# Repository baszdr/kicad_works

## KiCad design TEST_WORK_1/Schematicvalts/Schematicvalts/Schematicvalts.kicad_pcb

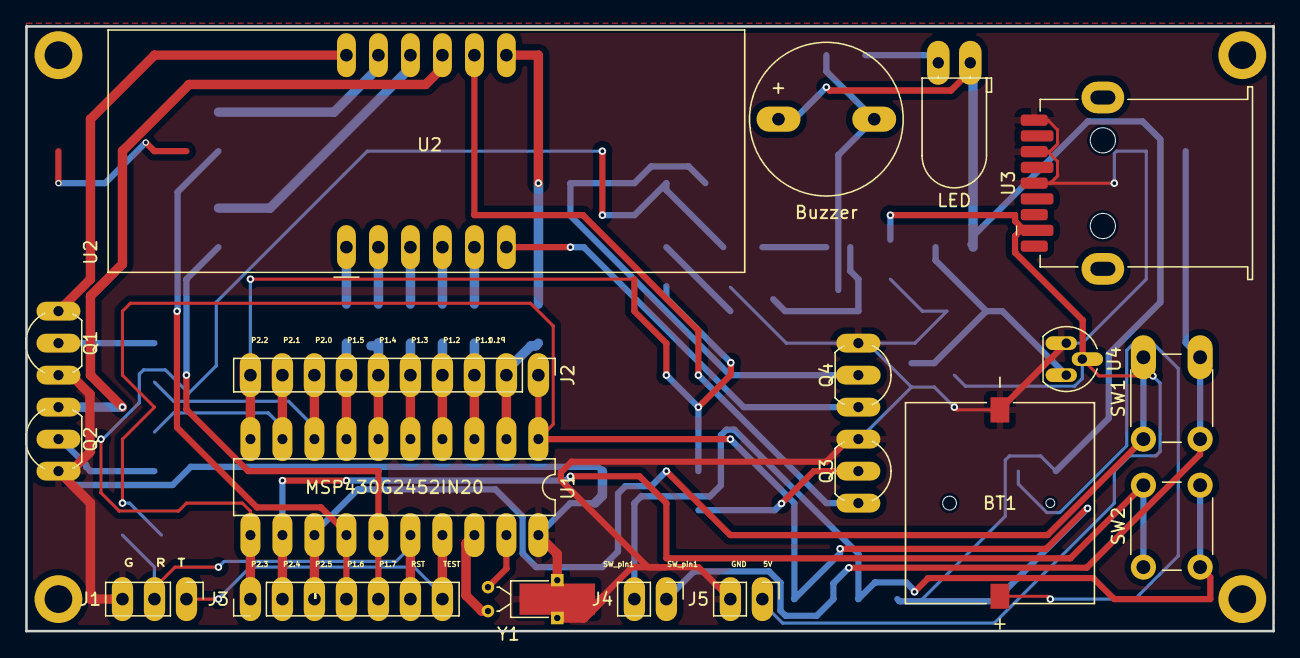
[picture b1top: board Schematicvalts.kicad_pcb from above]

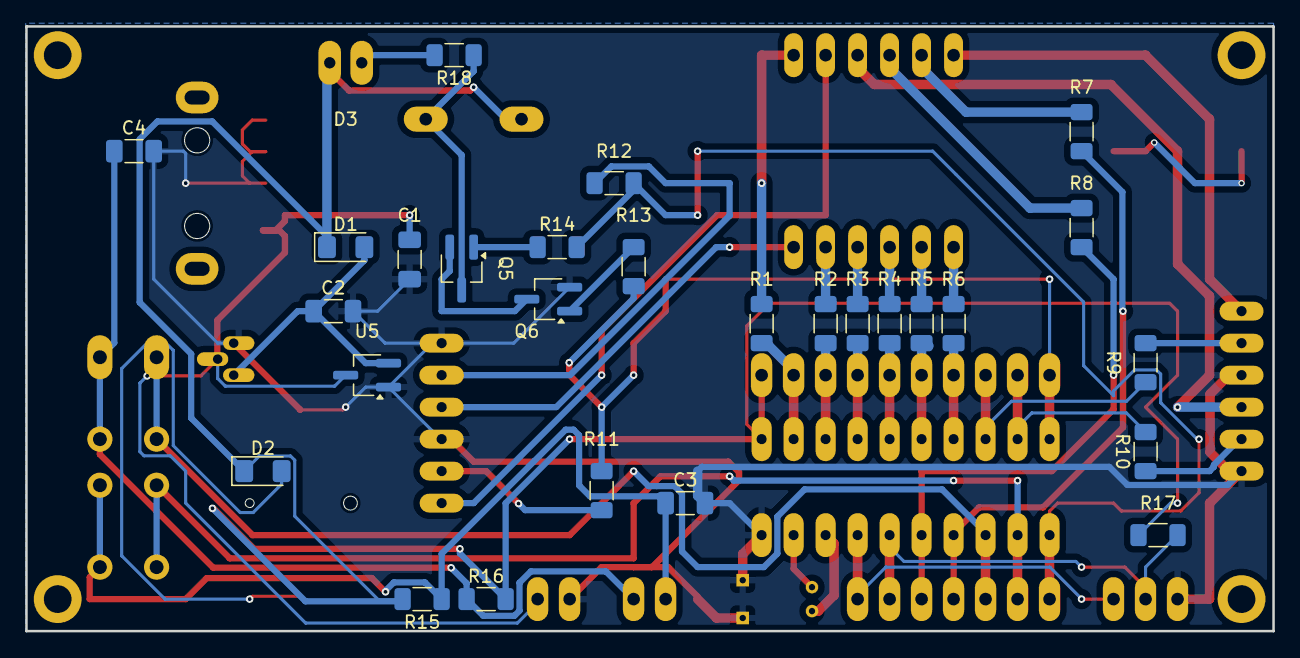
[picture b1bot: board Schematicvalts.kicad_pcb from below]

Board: 2 copper layers, 99.0 x 48.0 mm, 50 parts (27 on the bottom side), 46 nets.

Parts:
BT1: 1072; BAT_1072
BZ1: Buzzer; Buzzer_12x9.5RM7.6
C1, C2: 1uF; C_1206_3216Metric_Pad1.33x1.80mm_HandSolder
C3, C4: 470nF; C_1206_3216Metric_Pad1.33x1.80mm_HandSolder
D1, D2: D_Small; D_1206_3216Metric_Pad1.42x1.75mm_HandSolder
D3: LED; LED_D5.0mm_Horizontal_O1.27mm_Z3.0mm_Clear
H1, H2, H3, H4: MountingHole_Pad; MountingHole_2.2mm_M2_DIN965_Pad
J1: Conn_01x03_Socket; PinHeader_1x03_P2.54mm_Vertical
J2: Conn_01x10_Socket; PinHeader_1x10_P2.54mm_Vertical
J3: Conn_01x07_Socket; PinHeader_1x07_P2.54mm_Vertical
J4, J5: Conn_01x02_Socket; PinHeader_1x02_P2.54mm_Vertical
Q1, Q2, Q3, Q4: 2N3904; TO-92_Inline_Wide
Q5, Q6: MMBT3904; SOT-23W_Handsoldering
R1, R2, R3, R4, R5, R6, R7, R8: 300; R_1206_3216Metric_Pad1.30x1.75mm_HandSolder
R9, R10, R11, R12, R13, R14: 2.2k; R_1206_3216Metric_Pad1.30x1.75mm_HandSolder
R15, R16: 33k; R_1206_3216Metric_Pad1.30x1.75mm_HandSolder
R17: 51k; R_1206_3216Metric_Pad1.30x1.75mm_HandSolder
R18: 1K; R_1206_3216Metric_Pad1.30x1.75mm_HandSolder
SW1, SW2: SW_Push; SW_PUSH_6mm_H4.3mm
U1: MSP430G2452IN20; DIP-20_W7.62mm_LongPads
U2: CA56-12EWA
U3: 548190519; USB3_A_Receptacle_Wuerth_692122030100
U4: MCP1700x-120xxTO; TO-92L_HandSolder
U5: MCP1700x-120xxTT; SOT-23W_Handsoldering
Y1: Crystal_GND3; Crystal_DS26_D2.0mm_L6.0mm_Horizontal_1EP_style2

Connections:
/5V: C1.1, J5.1, U3.1 (VCC), U4.2 (VI), U5.3 (VI)
/P1.0: J2.2, R1.1, U1.2 (TA0CLK/ACLK/CA0/A0/P1.0)
/P1.1: J2.3, R2.1, U1.3 (TA0.0/CA1/A1/P1.1)
/P1.2: J2.4, R3.1, U1.4 (TA0.1/CA2/A2/P1.2)
/P1.3: J2.5, R4.1, U1.5 (ADC10CLK/VREF-/VeREF-/CAOUT/CA3/A3/P1.3)
/P1.4: J2.6, R5.1, U1.6 (TCK/SMCLK/TA0.2/VREF+/VeREF+/CA4/A4/P1.4)
/P1.5: J2.7, R6.1, U1.7 (TMS/SCLK/TA0.0/CA5/A5/P1.5)
/P1.6: J3.4, R7.1, U1.14 (TDI/TCLK/TA0.1/SDO/SCL/CA6/A6/P1.6)
/P1.7: J3.5, R8.1, U1.15 (TDO/TDI/SDI/SDA/CAOUT/CA7/A7/P1.7)
/P2.0: J2.8, R9.2, U1.8 (P2.0)
/P2.1: J2.9, R10.2, U1.9 (P2.1)
/P2.2: J2.10, R11.1, R13.2, U1.10 (P2.2)
/P2.3: J3.1, R12.1, R14.2, U1.11 (P2.3)
/P2.4: J3.2, SW2.1, U1.12 (P2.4)
/P2.5: J3.3, SW1.1, U1.13 (P2.5)
/P2.6: U1.19 (P2.6/XIN/TA0.1), Y1.2
/P2.7: U1.18 (P2.7/XOUT), Y1.1
/RST: J1.2, J3.6, R17.1, U1.16 (~RST/NMI/SBWTDIO)
/SW_pin: C4.1, J4.1, R16.1, SW1.2
/SW_pin1: C3.1, J4.2, R15.1, SW2.2
/TEST: J1.1, J3.7, U1.17 (SBWTCK/TEST)
GND: BT1.N, C1.2, C2.2, C3.2, C4.2, J1.3, J5.2, Q1.1 (E), Q2.1 (E), Q3.1 (E), Q4.1 (E), Q6.2 (E), U1.20 (DVSS), U3.5 (GND), U3.6, U3.7, U4.1 (GND), U5.1 (GND), Y1.3
unnamed: BZ1.2 (-), Q5.3 (C), R18.1
unnamed: C2.1, D1.2 (A), U4.3 (VO), U5.2 (VO)
unnamed: BT1.P, D2.2 (A)
unnamed: D3.1 (K), R18.2
unnamed: Q1.2 (B), R9.1
unnamed: Q1.3 (C), U2.12 (CA1)
unnamed: Q2.2 (B), R10.1
unnamed: Q2.3 (C), U2.9 (CA2)
unnamed: Q3.2 (B), R11.2
unnamed: Q3.3 (C), U2.8 (CA3)
unnamed: Q4.2 (B), R12.2
unnamed: Q4.3 (C), U2.6 (CA4)
unnamed: Q5.1 (B), R14.1
unnamed: Q5.2 (E), Q6.3 (C)
unnamed: Q6.1 (B), R13.1
unnamed: R4.2, U2.3 (DPX)
unnamed: R7.2, U2.11 (a)
unnamed: R1.2, U2.7 (b)
unnamed: R3.2, U2.4 (c)
unnamed: R5.2, U2.2 (d)
unnamed: R6.2, U2.1 (e)
unnamed: R8.2, U2.10 (f)
unnamed: R2.2, U2.5 (g)
VCC: BZ1.1 (+), D1.1 (K), D2.1 (K), D3.2 (A), J2.1, R15.2, R16.2, R17.2, U1.1 (DVCC)

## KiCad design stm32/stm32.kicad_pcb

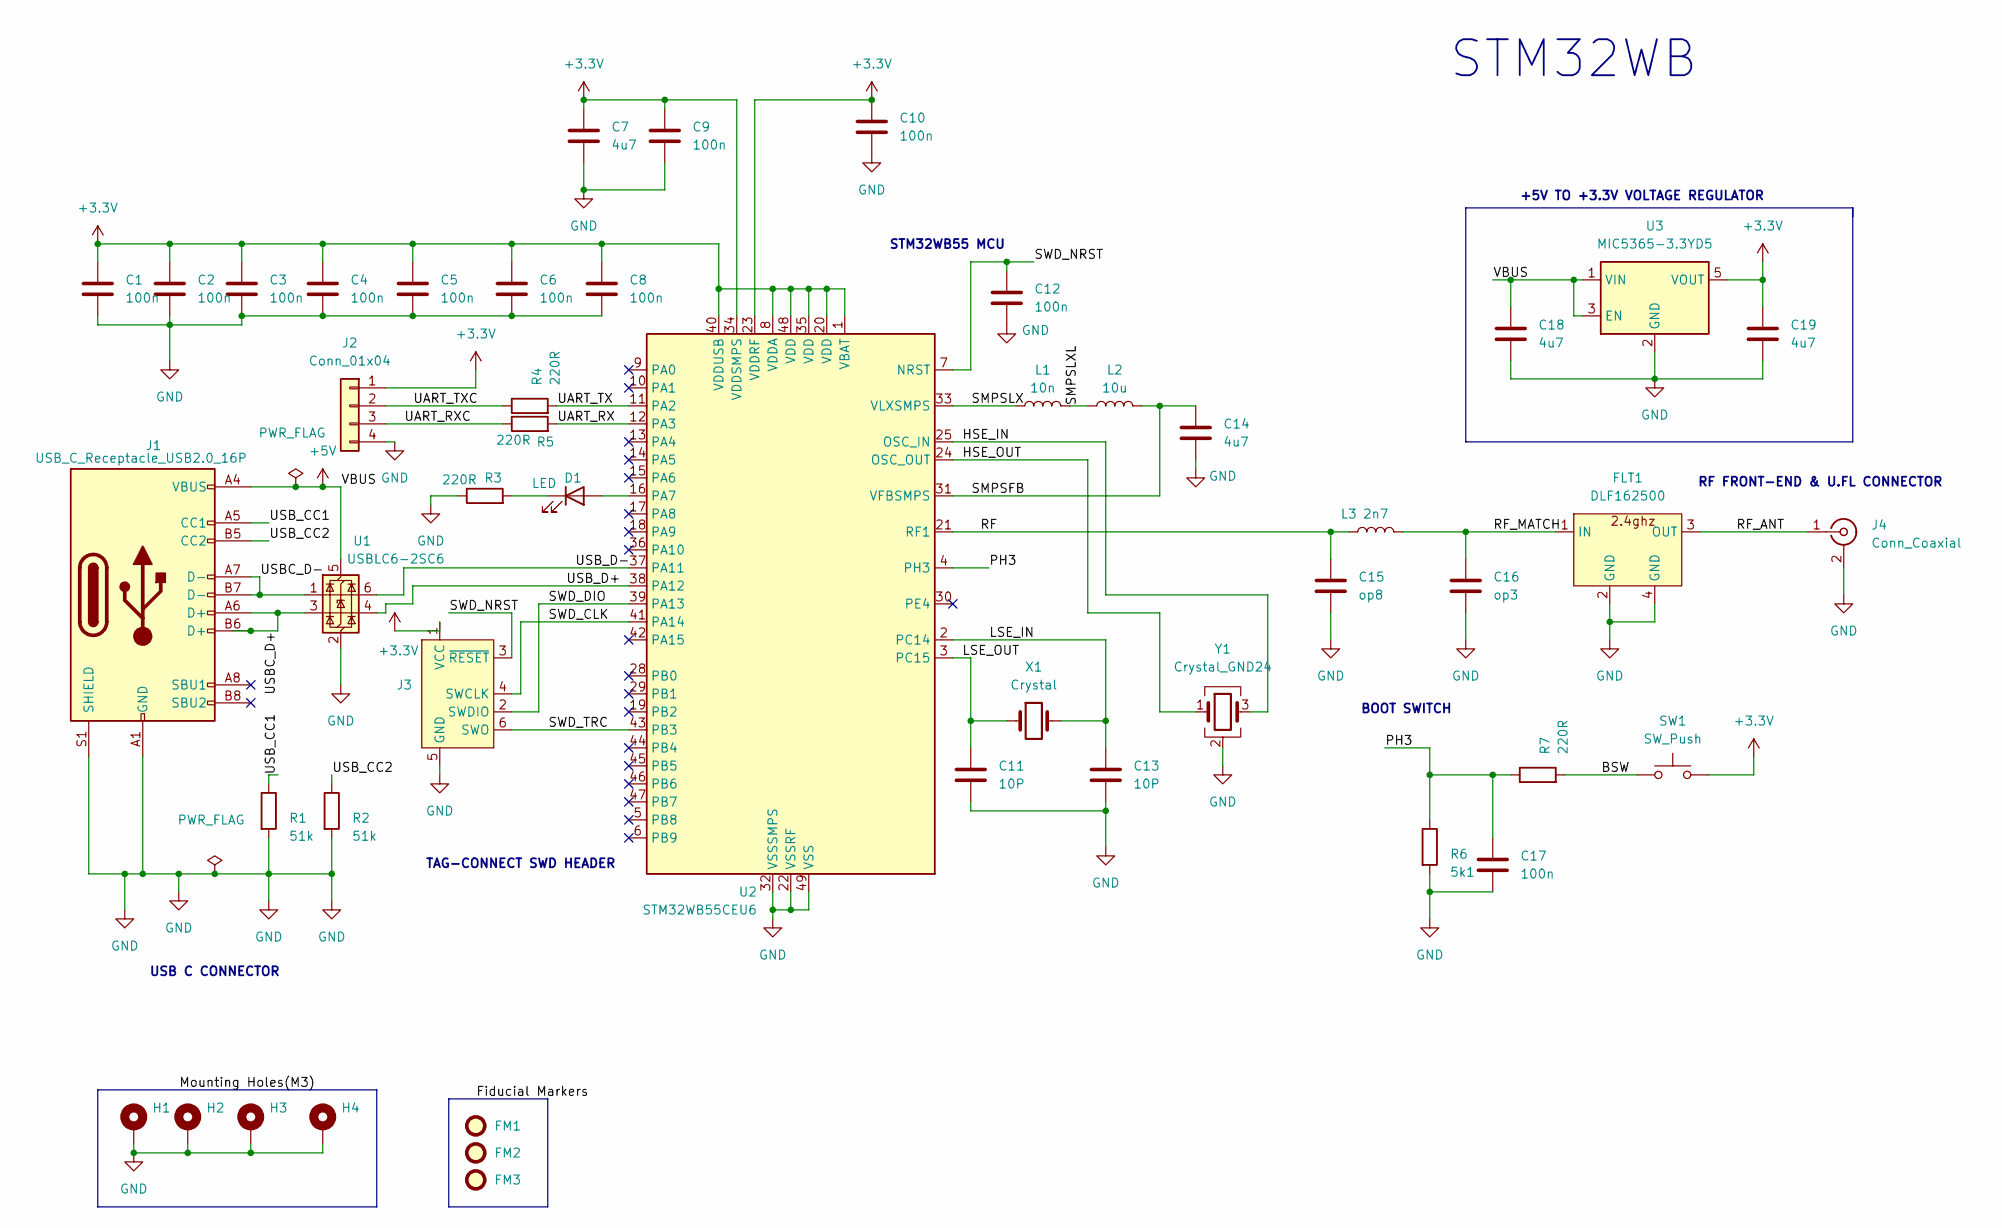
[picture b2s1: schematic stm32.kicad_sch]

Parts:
C1, C2, C3, C4, C5, C6, C8, C9, C10, C12, C17: 100n; C_0402_1005Metric
C7: 4u7; R_0402_1005Metric
C11, C13: 10P; C_0402_1005Metric
C14, C18, C19: 4u7; C_0603_1608Metric
C15: op8; C_0402_1005Metric
C16: op3; C_0402_1005Metric
D1: LED; L_0402_1005Metric
FLT1: DLF162500; Untitled
FM1, FM2, FM3: Fiducial; Fiducial_1mm_Mask2mm
H1, H2, H3, H4: MountingHole_Pad; MountingHole_2.2mm_M2_Pad_Via
J1: USB_C_Receptacle_USB2.0_16P; USB_C_Receptacle_GCT_USB4105-xx-A_16P_TopMnt_Horizontal
J2: Conn_01x04; Molex_CLIK-Mate_502386-0470_1x04-1MP_P1.25mm_Horizontal
J3: Tag-Connect_TC2030-IDC-FP_2x03_P1.27mm_Vertical
J4: Conn_Coaxial; U.FL_Hirose_U.FL-R-SMT-1_Vertical
L1: 10n; L_0402_1005Metric
L2: 10u; L_0402_1005Metric
L3: 2n7; L_0402_1005Metric
R1, R2: 51k; R_0402_1005Metric
R3, R4, R5, R7: 220R; R_0402_1005Metric
R6: 5k1; R_0402_1005Metric
SW1: SW_Push; SW_SPST_CK_RS282G05A3
U1: USBLC6-2SC6; SOT-23-6
U2: STM32WB55CEU6; QFN-48-1EP_7x7mm_P0.5mm_EP5.6x5.6mm
U3: MIC5365-3.3YD5; TSOT-23-5
X1: Crystal; Crystal_SMD_2012-2Pin_2.0x1.2mm
Y1: Crystal_GND24; Crystal_SMD_2016-4Pin_2.0x1.6mm

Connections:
+3.3V: C1.1, C2.1, C3.1, C4.1, C5.1, C6.1, C7.1, C8.1, C9.1, C10.1, C19.1, J2.1, J3.1 (VCC), SW1.2, U2.1 (VBAT), U2.8 (VDDA), U2.20 (VDD), U2.23 (VDDRF), U2.34 (VDDSMPS), U2.35 (VDD), U2.40 (VDDUSB), U2.48 (VDD), U3.5 (VOUT)
+5V: C18.1, J1.A4 (VBUS), J1.A9 (VBUS), J1.B4 (VBUS), J1.B9 (VBUS), U1.5 (VBUS), U3.1 (VIN), U3.3 (EN)
/BSW: R7.2, SW1.1
/HSE_IN: U2.25 (OSC_IN), Y1.3
/HSE_OUT: U2.24 (OSC_OUT), Y1.1
/LSE_IN: C13.1, U2.2 (PC14), X1.2
/LSE_OUT: C11.1, U2.3 (PC15), X1.1
/PH3: C17.1, R6.1, R7.1, U2.4 (PH3)
/RF: C15.1, L3.1, U2.21 (RF1)
/RF_ANT: FLT1.3 (OUT), J4.1 (In)
/RF_MATCH: C16.1, FLT1.1 (IN), L3.2
/SMPSFB: C14.1, L2.2, U2.31 (VFBSMPS)
/SMPSLX: L1.1, U2.33 (VLXSMPS)
/SMPSLXL: L1.2, L2.1
/SWD_CLK: J3.4 (SWCLK), U2.41 (PA14)
/SWD_DIO: J3.2 (SWDIO), U2.39 (PA13)
/SWD_NRST: C12.1, J3.3 (~RESET), U2.7 (NRST)
/SWD_TRC: J3.6 (SWO), U2.43 (PB3)
/UART_RX: R5.2, U2.12 (PA3)
/UART_RXC: J2.3, R5.1
/UART_TX: R4.2, U2.11 (PA2)
/UART_TXC: J2.2, R4.1
/USBC_D+: J1.A6 (D+), J1.B6 (D+), U1.3 (I/O2)
/USBC_D-: J1.A7 (D-), J1.B7 (D-), U1.1 (I/O1)
/USB_CC1: J1.A5 (CC1), R1.1
/USB_CC2: J1.B5 (CC2), R2.1
/USB_D+: U1.4 (I/O2), U2.38 (PA12)
/USB_D-: U1.6 (I/O1), U2.37 (PA11)
GND: C1.2, C2.2, C3.2, C4.2, C5.2, C6.2, C7.2, C8.2, C9.2, C10.2, C11.2, C12.2, C13.2, C14.2, C15.2, C16.2, C17.2, C18.2, C19.2, FLT1.2 (GND), FLT1.4 (GND), H1.1, H2.1, H3.1, H4.1, J1.A1 (GND), J1.A12 (GND), J1.B1 (GND), J1.B12 (GND), J1.S1 (SHIELD), J2.4, J3.5 (GND), J4.2 (Ext), R1.2, R2.2, R3.1, R6.2, U1.2 (GND), U2.22 (VSSRF), U2.32 (VSSSMPS), U2.49 (VSS), U3.2 (GND), Y1.2 (G), Y1.4 (G)
unnamed: D1.2 (A), U2.16 (PA7)
unnamed: D1.1 (K), R3.2

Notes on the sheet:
+5V TO +3.3V VOLTAGE REGULATOR
RF FRONT-END & U.FL CONNECTOR
TAG-CONNECT SWD HEADER
USB C CONNECTOR
STM32WB
STM32WB55 MCU
BOOT SWITCH

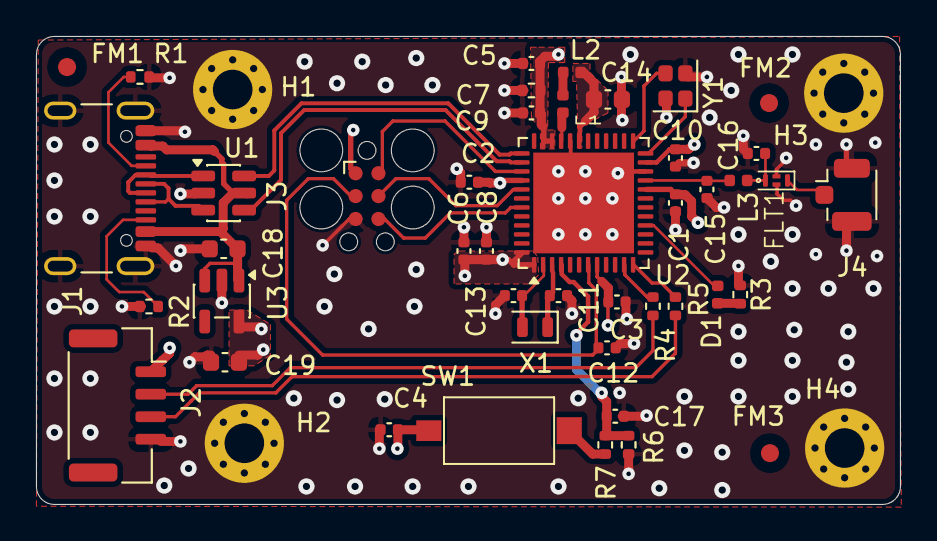
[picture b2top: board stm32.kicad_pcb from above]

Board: 4 copper layers, 48.0 x 26.0 mm, 48 parts (0 on the bottom side), 31 nets.

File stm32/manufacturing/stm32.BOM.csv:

"Source:","C:\Users\smbna\OneDrive - Rīgas Tehniskā Universitāte\Dokumenti\KiCad\stm32\stm32.kicad_sch"
"Date:","2026-04-02T17:49:33+0300"
"Tool:","Eeschema 9.0.7"
"Generator:","C:\Program Files\KiCad\9.0\bin\scripting\plugins/bom_csv_grouped_by_value_with_fp.py"
"Component Count:","48"
"Ref","Qnty","Value","Cmp name","Footprint","Description","Vendor","DNP"
"C1, C2, C3, C4, C5, C6, C8, C9, C10, C12, C17","11","100n","C","Capacitor_SMD:C_0402_1005Metric","Unpolarized capacitor","",""
"C7","1","4u7","C","Resistor_SMD:R_0402_1005Metric","Unpolarized capacitor","",""
"C11, C13","2","10P","C","Capacitor_SMD:C_0402_1005Metric","Unpolarized capacitor","",""
"C14, C18, C19","3","4u7","C","Capacitor_SMD:C_0603_1608Metric","Unpolarized capacitor","",""
"C15","1","op8","C","Capacitor_SMD:C_0402_1005Metric","Unpolarized capacitor","",""
"C16","1","op3","C","Capacitor_SMD:C_0402_1005Metric","Unpolarized capacitor","",""
"D1","1","LED","LED","Inductor_SMD:L_0402_1005Metric","Light emitting diode","",""
"FLT1","1","DLF162500","DLF162500LT","BLUEPRINT:Untitled","","",""
"FM1, FM2, FM3","3","Fiducial","Fiducial","Fiducial:Fiducial_1mm_Mask2mm","Fiducial Marker","",""
"H1, H2, H3, H4","4","MountingHole_Pad","MountingHole_Pad","MountingHole:MountingHole_2.2mm_M2_Pad_Via","Mounting Hole with connection","",""
"J1","1","USB_C_Receptacle_USB2.0_16P","USB_C_Receptacle_USB2.0_16P","Connector_USB:USB_C_Receptacle_GCT_USB4105-xx-A_16P_TopMnt_Horizontal","USB 2.0-only 16P Type-C Receptacle connector","",""
"J2","1","Conn_01x04","Conn_01x04","Connector_Molex:Molex_CLIK-Mate_502386-0470_1x04-1MP_P1.25mm_Horizontal","Generic connector, single row, 01x04, script generated (kicad-library-utils/schlib/autogen/connector/)","",""
"J3","1","~","Conn_ARM_SWD_TagConnect_TC2030","Connector:Tag-Connect_TC2030-IDC-FP_2x03_P1.27mm_Vertical","Tag-Connect ARM Cortex SWD JTAG connector, 6 pin","",""
"J4","1","Conn_Coaxial","Conn_Coaxial","Connector_Coaxial:U.FL_Hirose_U.FL-R-SMT-1_Vertical","coaxial connector (BNC, SMA, SMB, SMC, Cinch/RCA, LEMO, ...)","",""
"L1","1","10n","L","Inductor_SMD:L_0402_1005Metric","Inductor","",""
"L2","1","10u","L","Inductor_SMD:L_0402_1005Metric","Inductor","",""
"L3","1","2n7","L","Inductor_SMD:L_0402_1005Metric","Inductor","",""
"R1, R2","2","51k","R","Resistor_SMD:R_0402_1005Metric","Resistor","",""
"R3, R4, R5, R7","4","220R","R","Resistor_SMD:R_0402_1005Metric","Resistor","",""
"R6","1","5k1","R","Resistor_SMD:R_0402_1005Metric","Resistor","",""
"SW1","1","SW_Push","SW_Push","Button_Switch_SMD:SW_SPST_CK_RS282G05A3","Push button switch, generic, two pins","",""
"U1","1","USBLC6-2SC6","USBLC6-2SC6","Package_TO_SOT_SMD:SOT-23-6","Very low capacitance ESD protection diode, 2 data-line, SOT-23-6","",""
"U2","1","STM32WB55CEU6","STM32WB55CEUx","Package_DFN_QFN:QFN-48-1EP_7x7mm_P0.5mm_EP5.6x5.6mm","STMicroelectronics Arm Cortex-M4 MCU, 512KB flash, 256KB RAM, 64 MHz, 1.71-3.6V, 30 GPIO, UFQFPN48","",""
"U3","1","MIC5365-3.3YD5","MIC5365-3.3YD5","Package_TO_SOT_SMD:TSOT-23-5","150mA Low-dropout Voltage Regulator, Vout 3.3V, Vin up to 5.5V, TSOT-23-5","",""
"X1","1","Crystal","Crystal","Crystal:Crystal_SMD_2012-2Pin_2.0x1.2mm","Two pin crystal","",""
"Y1","1","Crystal_GND24","Crystal_GND24","Crystal:Crystal_SMD_2016-4Pin_2.0x1.6mm","Four pin crystal, GND on pins 2 and 4","",""

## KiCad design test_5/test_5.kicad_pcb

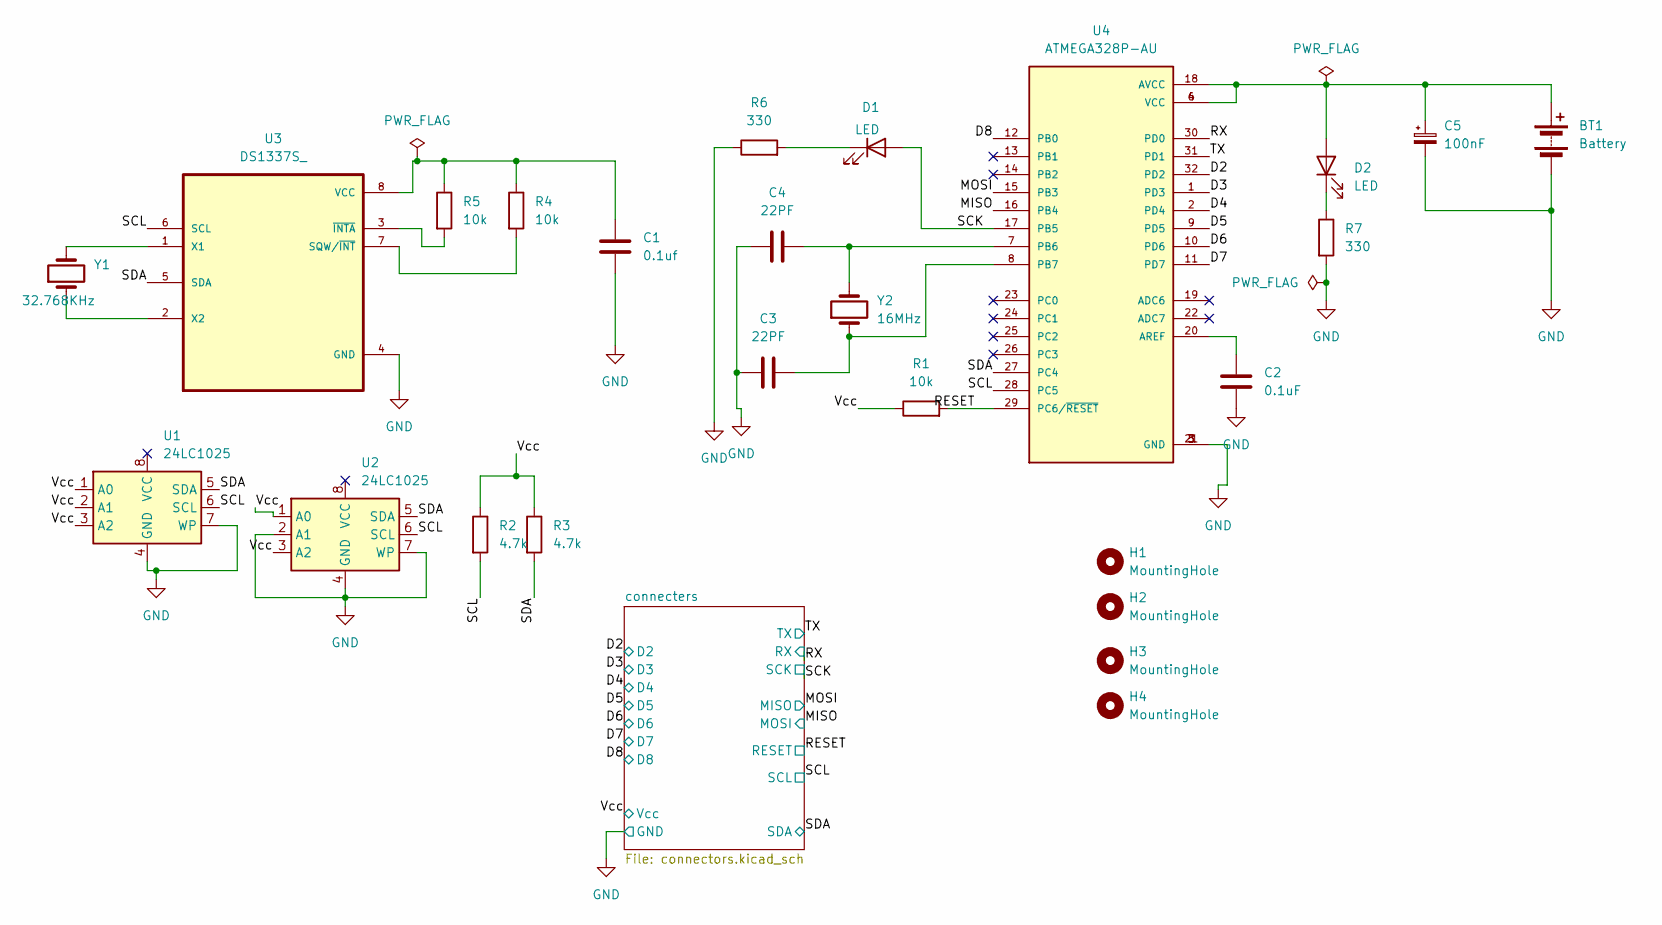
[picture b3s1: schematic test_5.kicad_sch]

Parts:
BT1: Battery; PinHeader_1x02_P2.54mm_Vertical
C1: 0.1uf; C_0805_2012Metric
C2: 0.1uF; C_0805_2012Metric
C3, C4: 22PF; C_0805_2012Metric
C5: 100nF; C_0805_2012Metric
D1, D2: LED; LED_0805_2012Metric
H1, H2, H3, H4: MountingHole; MountingHole_2.1mm
R1, R4, R5: 10k; R_0805_2012Metric
R2, R3: 4.7k; R_0805_2012Metric
R6: 330; R_0805_2012Metric
R7: 330; R_0815_2038Metric
U1, U2: 24LC1025; DIP787W46P254L927H533Q8
U3: DS1337S_; SOIC127P600X175-8N
U4: ATMEGA328P-AU; QFP80P900X900X120-32N; PARTREV 8271A
Y1: 32.768KHz; Crystal_SMD_5032-2Pin_5.0x3.2mm_HandSoldering
Y2: 16MHz; Crystal_SMD_5032-2Pin_5.0x3.2mm_HandSoldering

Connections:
/D2: U4.32 (PD2); also elsewhere on the board
/D3: U4.1 (PD3); also elsewhere on the board
/D4: U4.2 (PD4); also elsewhere on the board
/D5: U4.9 (PD5); also elsewhere on the board
/D6: U4.10 (PD6); also elsewhere on the board
/D7: U4.11 (PD7); also elsewhere on the board
/D8: U4.12 (PB0); also elsewhere on the board
/MISO: U4.16 (PB4); also elsewhere on the board
/MOSI: U4.15 (PB3); also elsewhere on the board
/RESET: R1.2, U4.29 (PC6/~RESET); also elsewhere on the board
/RX: U4.30 (PD0); also elsewhere on the board
/SCK: D1.2 (A), U4.17 (PB5); also elsewhere on the board
/SCL: R2.2, U1.6 (SCL), U2.6 (SCL), U3.6 (SCL), U4.28 (PC5); also elsewhere on the board
/SDA: R3.2, U1.5 (SDA), U2.5 (SDA), U3.5 (SDA), U4.27 (PC4); also elsewhere on the board
/TX: U4.31 (PD1); also elsewhere on the board
/Vcc: R1.1, R2.1, R3.1, U1.1 (A0), U1.2 (A1), U1.3 (A2), U2.1 (A0), U2.3 (A2); also elsewhere on the board
GND: BT1.2 (-), C1.1, C2.1, C3.1, C4.2, C5.2, R6.1, R7.2, U1.4 (GND), U1.7 (WP), U2.2 (A1), U2.4 (GND), U2.7 (WP), U3.4 (GND), U4.3 (GND), U4.5 (GND), U4.21 (GND); also elsewhere on the board
unnamed: BT1.1 (+), C5.1, D2.2 (A), U4.4 (VCC), U4.6 (VCC), U4.18 (AVCC)
unnamed: D1.1 (K), R6.2
unnamed: D2.1 (K), R7.1
unnamed: R4.2, U3.7 (SQW/~INT)
unnamed: C1.2, R4.1, R5.1, U3.8 (VCC)
unnamed: U3.1 (X1), Y1.2
unnamed: U3.2 (X2), Y1.1
unnamed: R5.2, U3.3 (~INTA)
unnamed: C2.2, U4.20 (AREF)
unnamed: C4.1, U4.7 (PB6), Y2.2
unnamed: C3.2, U4.8 (PB7), Y2.1

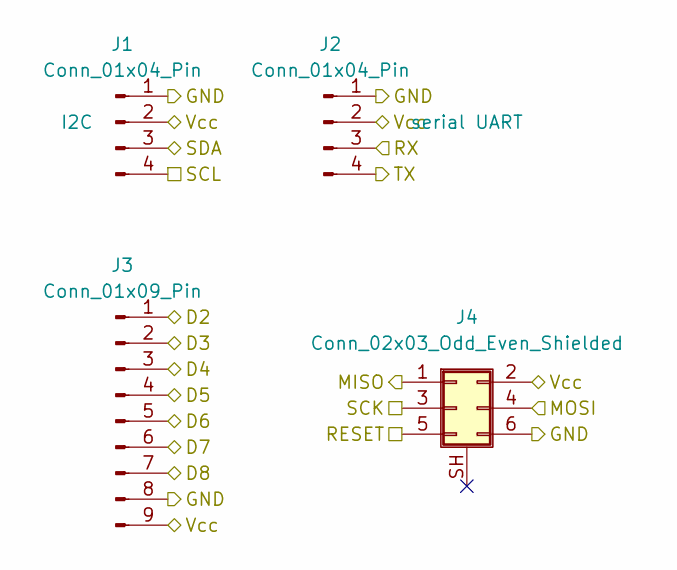
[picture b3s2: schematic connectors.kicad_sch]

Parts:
J1, J2: Conn_01x04_Pin; PinHeader_1x04_P2.54mm_Vertical
J3: Conn_01x09_Pin; PinHeader_1x09_P2.54mm_Vertical
J4: Conn_02x03_Odd_Even_Shielded; PinHeader_2x03_P2.54mm_Vertical

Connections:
/D2: J3.1; also elsewhere on the board
/D3: J3.2; also elsewhere on the board
/D4: J3.3; also elsewhere on the board
/D5: J3.4; also elsewhere on the board
/D6: J3.5; also elsewhere on the board
/D7: J3.6; also elsewhere on the board
/D8: J3.7; also elsewhere on the board
/MISO: J4.4; also elsewhere on the board
/MOSI: J4.1; also elsewhere on the board
/RESET: J4.5; also elsewhere on the board
/RX: J2.3; also elsewhere on the board
/SCK: J4.3; also elsewhere on the board
/SCL: J1.4; also elsewhere on the board
/SDA: J1.3; also elsewhere on the board
/TX: J2.4; also elsewhere on the board
/Vcc: J1.2, J2.2, J3.9, J4.2; also elsewhere on the board
GND: J1.1, J2.1, J3.8, J4.6; also elsewhere on the board

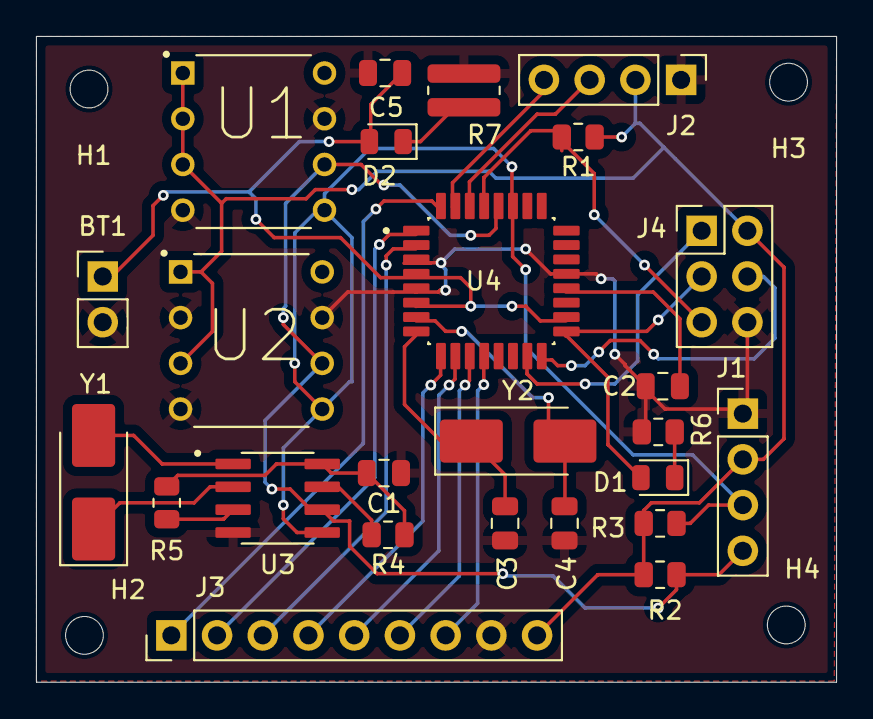
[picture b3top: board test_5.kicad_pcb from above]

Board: 2 copper layers, 44.4 x 35.9 mm, 29 parts (0 on the bottom side), 28 nets.

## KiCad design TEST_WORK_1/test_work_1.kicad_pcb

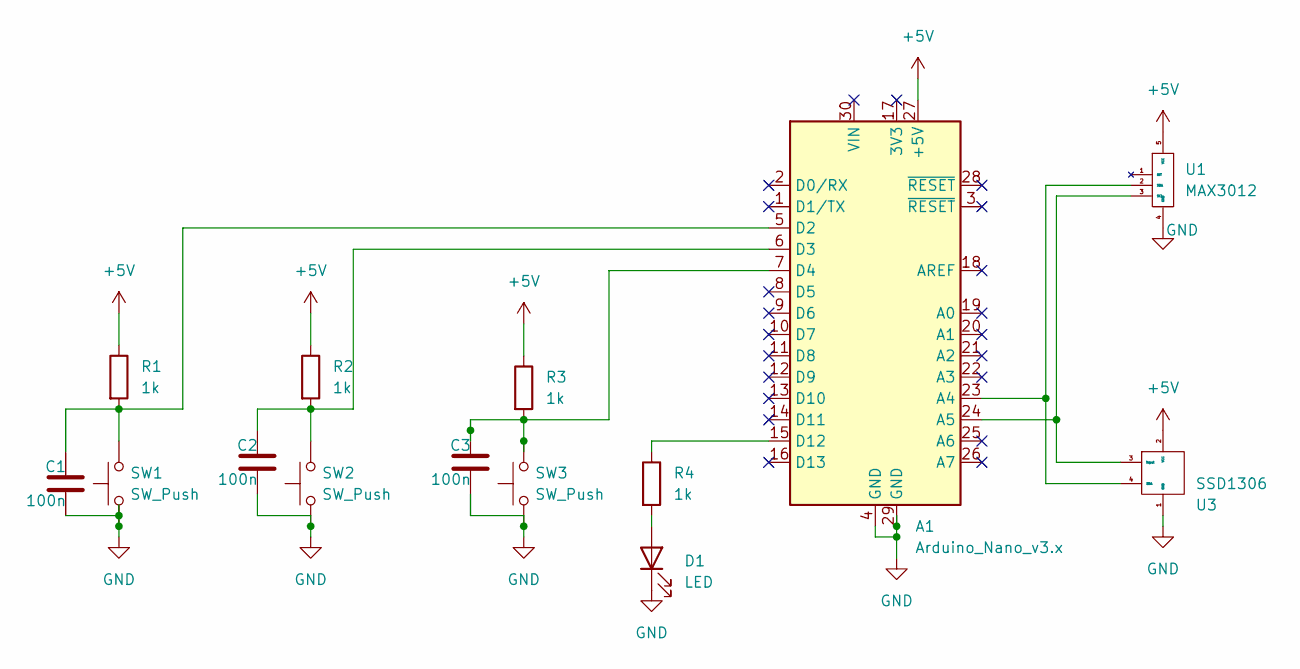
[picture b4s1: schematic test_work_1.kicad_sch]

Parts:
A1: Arduino_Nano_v3.x; Arduino_Nano
C1, C2, C3: 100n; C_Disc_D4.7mm_W2.5mm_P5.00mm
D1: LED; LED_D5.0mm
R1, R2, R3, R4: 1k; R_Axial_DIN0204_L3.6mm_D1.6mm_P7.62mm_Horizontal
SW1, SW2, SW3: SW_Push; SW_PUSH_6mm
U1: MAX3012; Untitled
U3: SSD1306; Untitled_1

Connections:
+5V: A1.27 (+5V), R1.1, R2.1, R3.1, U1.5 (VCC), U3.2 (VCC)
GND: A1.4 (GND), A1.29 (GND), C1.1, C2.1, C3.1, D1.1 (K), SW1.1, SW2.1, SW3.1, U1.4 (GND), U3.1 (GND)
unnamed: A1.23 (A4), U1.2 (SDA), U3.4 (SDA)
unnamed: A1.24 (A5), U1.3 (SCL), U3.3 (input)
unnamed: A1.5 (D2), C1.2, R1.2, SW1.2
unnamed: A1.6 (D3), C2.2, R2.2, SW2.2
unnamed: A1.7 (D4), C3.2, R3.2, SW3.2
unnamed: A1.15 (D12), R4.1
unnamed: D1.2 (A), R4.2

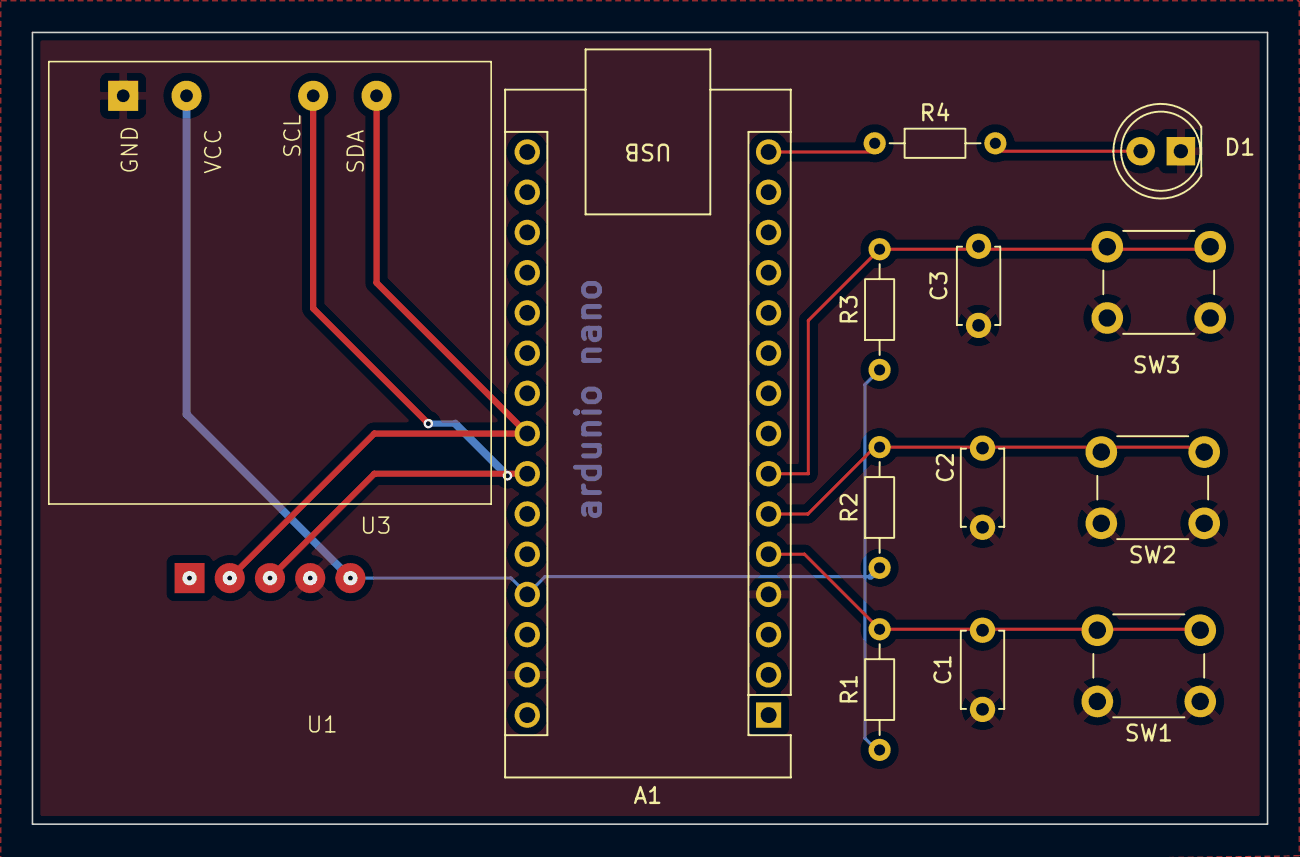
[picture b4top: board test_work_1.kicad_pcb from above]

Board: 4 copper layers, 78.0 x 50.0 mm, 14 parts (0 on the bottom side), 9 nets.

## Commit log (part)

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2025-10-14 Day_01
2025-10-14 Test_01
2025-11-20 Add test_work_5 for Kicad software practice
    This file includes the test work 5 of the practising work of Kicad software
2025-11-20 day5
2026-04-06 Upload KiCad design with all folders
